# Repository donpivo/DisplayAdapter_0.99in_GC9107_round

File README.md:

Description: https://retronics.no/2024/07/14/diy-breadboard-adapter-for-0-99-circular-display-with-gc9107-controller/

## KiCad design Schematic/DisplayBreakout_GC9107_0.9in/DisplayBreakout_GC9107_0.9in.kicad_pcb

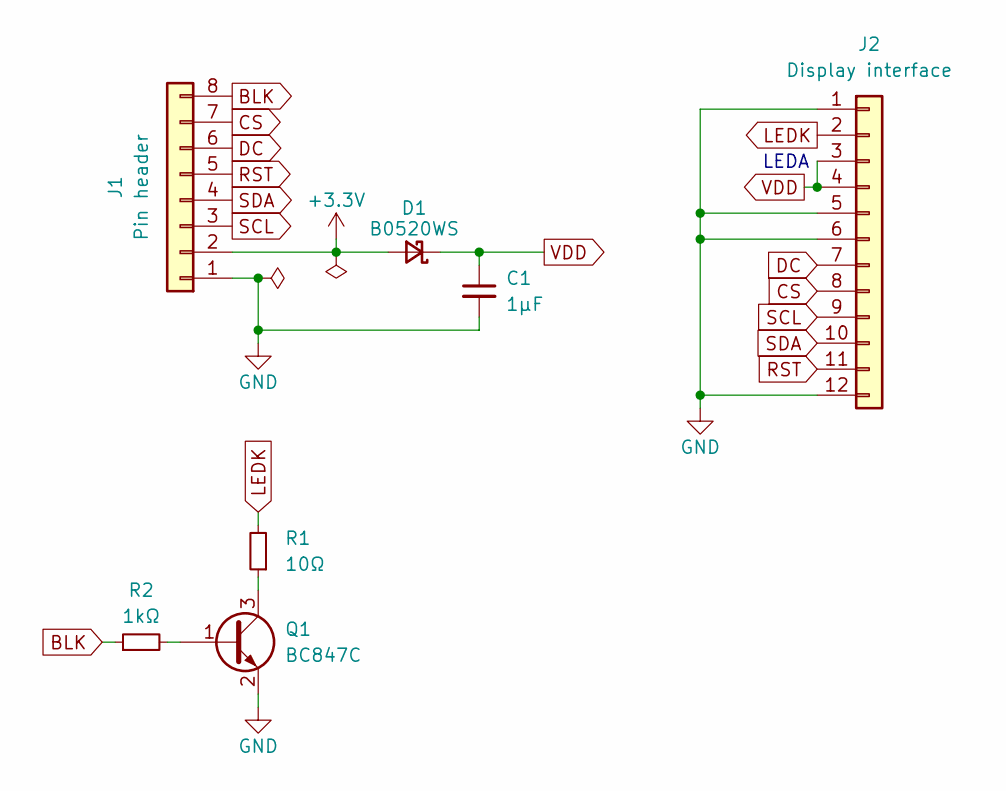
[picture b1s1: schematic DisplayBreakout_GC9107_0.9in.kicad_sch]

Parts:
C1: 1µF; C_0603_1608Metric_Pad1.08x0.95mm_HandSolder
D1: B0520WS; D_SOD-323_HandSoldering
J1: Pin header; PinHeader_1x08_P2.54mm_Vertical
J2: Display interface; 505110-1292
Q1: BC847C; SOT-23
R1: 10Ω; R_0603_1608Metric_Pad0.98x0.95mm_HandSolder
R2: 1kΩ; R_0603_1608Metric_Pad0.98x0.95mm_HandSolder

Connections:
+3.3V: D1.2 (A), J1.2
BLK: J1.8, R2.1
CS: J1.7, J2.8
DC: J1.6, J2.7
GND: C1.2, J1.1, J2.1, J2.5, J2.6, J2.12, Q1.2 (E)
LEDK: J2.2, R1.2
unnamed: Q1.1 (B), R2.2
unnamed: Q1.3 (C), R1.1
RST: J1.5, J2.11
SCL: J1.3, J2.9
SDA: J1.4, J2.10
VDD: C1.1, D1.1 (K), J2.3, J2.4

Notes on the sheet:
LEDA

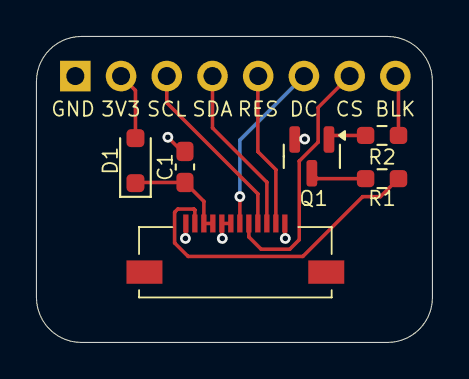
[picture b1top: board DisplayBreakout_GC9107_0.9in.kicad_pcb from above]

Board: 2 copper layers, 22.0 x 17.0 mm, 7 parts (1 on the bottom side), 12 nets.

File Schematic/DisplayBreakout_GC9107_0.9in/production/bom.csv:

Designator,Footprint,Quantity,Value,LCSC Part #
C1,0603,1,1µF,
D1,D_SOD-323_HandSoldering,1,B0520WS,
J1,PinHeader_1x08_P2.54mm_Vertical,1,Pin header,
J2,505110-1292,1,Display interface,
Q1,SOT-23,1,BC847,
R1,0603,1,10Ω,
R2,0603,1,1kΩ,

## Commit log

2025-07-05 Fixed display initiation to avoid random pixels
2025-07-05 Updated display initialization to avoid random pixels
